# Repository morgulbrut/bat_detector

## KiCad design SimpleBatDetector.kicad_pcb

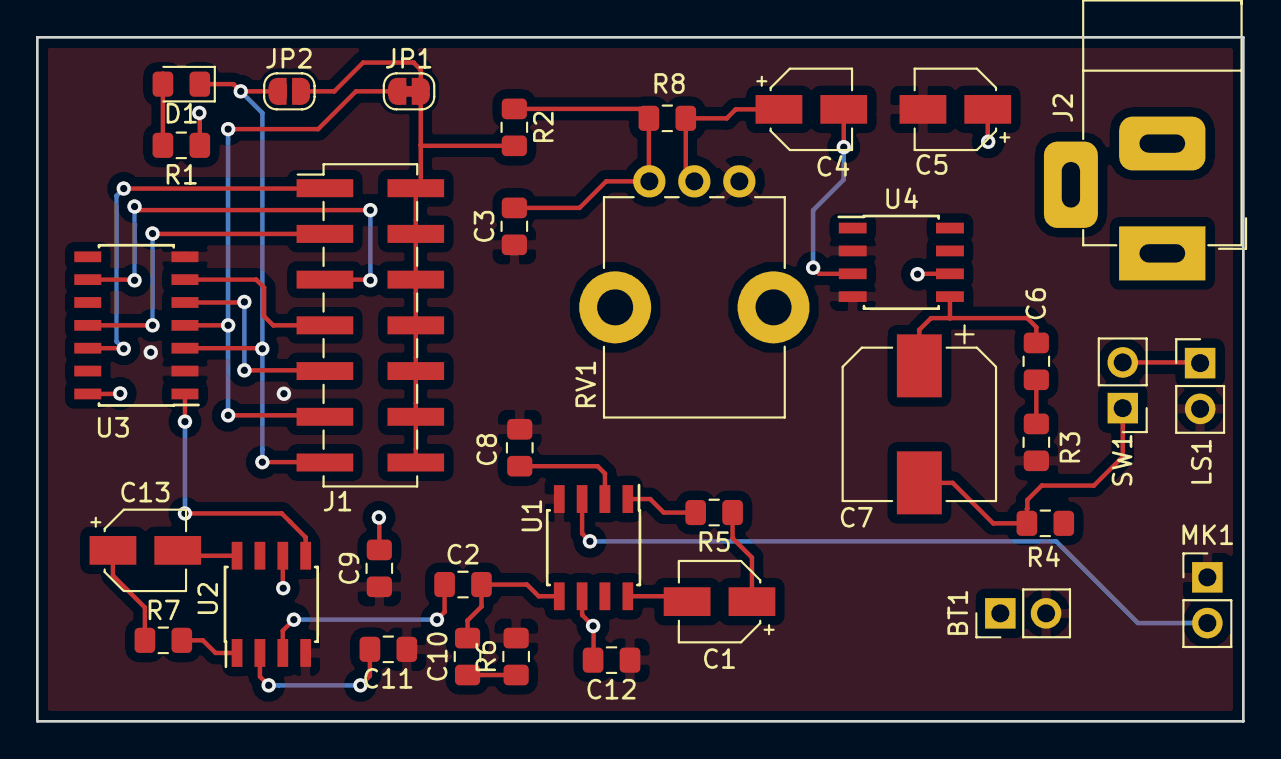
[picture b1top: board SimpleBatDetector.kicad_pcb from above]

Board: 2 copper layers, 67.0 x 38.0 mm, 35 parts (0 on the bottom side), 31 nets.

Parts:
BT1: Battery; PinHeader_1x02_P2.54mm_Vertical
C1, C5, C13: 10u; CP_Elec_4x5.4
C2, C3, C6, C10: 47n; C_0805_2012Metric_Pad1.15x1.40mm_HandSolder
C4: 4.7u; CP_Elec_4x5.4
C7: 220u; CP_Elec_8x10
C8, C11: 22n; C_0805_2012Metric_Pad1.15x1.40mm_HandSolder
C9, C12: 100n; C_0805_2012Metric_Pad1.15x1.40mm_HandSolder
D1: LED_Small_ALT; LED_0805_2012Metric_Pad1.15x1.40mm_HandSolder
J1: Conn_02x07_Odd_Even; PinHeader_2x07_P2.54mm_Vertical_SMD
J2: AudioJack3_Ground; Jack_Horizontal
JP1: SolderJumper_2_Bridged; SolderJumper-2_P1.3mm_Bridged_RoundedPad1.0x1.5mm
JP2: SolderJumper_2_Open; SolderJumper-2_P1.3mm_Open_RoundedPad1.0x1.5mm
LS1: Speaker; PinHeader_1x02_P2.54mm_Vertical
MK1: Microphone_Ultrasound; PinHeader_1x02_P2.54mm_Vertical
R1, R3, R5, R6, R7: TBD; R_0805_2012Metric_Pad1.15x1.40mm_HandSolder
R2, R8: 10k; R_0805_2012Metric_Pad1.15x1.40mm_HandSolder
R4: 1k; R_0805_2012Metric_Pad1.15x1.40mm_HandSolder
RV1: 10k log; Potentiometer_Alps_RK09K_Single_Vertical
SW1: SW_Push; PinHeader_1x02_P2.54mm_Vertical
U1, U2, U4: LM386; SOIC-8_3.9x4.9mm_P1.27mm
U3: 4024; SOIC-14_3.9x8.7mm_P1.27mm

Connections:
+9V: BT1.1, C5.1, C9.2, C12.2, R1.1, U1.6, U2.6, U3.14, U4.6
GND: BT1.2, C3.1, C5.2, C8.1, C9.1, C11.1, C12.1, LS1.2, MK1.1, R3.2, R6.2, RV1.3, U1.4, U2.4, U3.2, U3.7, U4.2, U4.4
unnamed: C1.1, R5.1
unnamed: C1.2, U1.8
unnamed: C2.1, U2.3
unnamed: C3.2, R2.1, R8.2, RV1.1
unnamed: C4.1, R8.1, RV1.2
unnamed: C4.2, U4.3
unnamed: C6.1, R3.1
unnamed: C6.2, C7.1, U4.5
unnamed: C7.2, R4.2, SW1.1
unnamed: C8.2, U1.2
unnamed: C10.1, R6.1
unnamed: C2.2, C10.2, U1.5
unnamed: C11.2, U2.2
unnamed: C13.1, R7.1
unnamed: C13.2, U2.8
unnamed: D1.1, J1.13, JP2.1, U3.3
unnamed: D1.2, R1.2
unnamed: J1.1, U3.12
unnamed: J1.3, U3.11
unnamed: J1.5, U3.9
unnamed: J1.7, U3.6
unnamed: J1.9, U3.5
unnamed: J1.2, J1.4, J1.6, J1.8, J1.10, J1.12, J1.14, JP1.2, JP2.2, R2.2
unnamed: J1.11, JP1.1, U3.4
unnamed: LS1.1, SW1.2
unnamed: MK1.2, U1.3
unnamed: R5.2, U1.1
unnamed: R7.2, U2.1
unnamed: U2.5, U3.1

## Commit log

2018-10-30 initial
2018-10-31 added BOM
